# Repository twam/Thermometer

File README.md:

# Thermometer

## Sensor-Board

Connector: [Omega PCC-SMP-K](https://www.omega.com/en-us/temperature-measurement/temperature-connectors%2C-panels-and-block-assemblies/temperature-connectors/p/PCC-OST-SMP)

Chip: [MAX31856](https://datasheets.maximintegrated.com/en/ds/MAX31856.pdf)

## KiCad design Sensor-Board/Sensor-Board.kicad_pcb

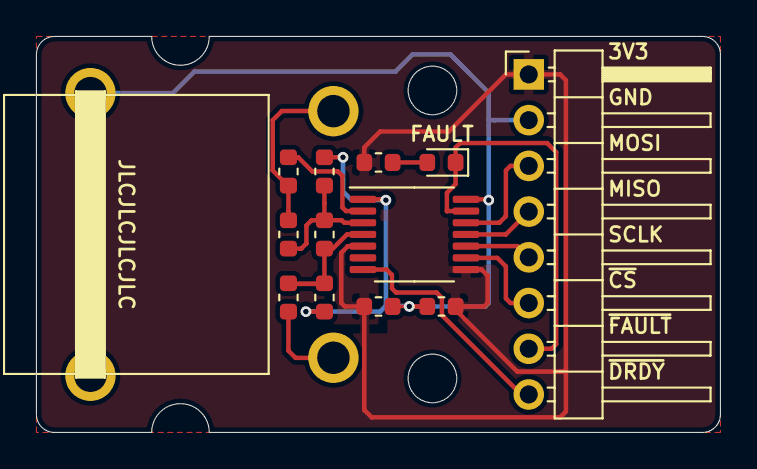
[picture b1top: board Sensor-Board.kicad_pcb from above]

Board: 2 copper layers, 38.0 x 22.0 mm, 13 parts (0 on the bottom side), 14 nets.

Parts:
C11, C12, C13, C14, C15: 100n/50V; C_0603_1608Metric
D11: Red; LED_0603_1608Metric
J1: Sensor; PCC-SMP-K
J2: Conn_01x08; PinHeader_1x08_P2.54mm_Horizontal
R11, R12, R13, R14: R_Small; R_0603_1608Metric
U1: MAX31856; TSSOP-14_4.4x5mm_P0.65mm

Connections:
+3V3: C11.1, C12.1, J2.1, R14.1, U1.5, U1.8
/MISO: J2.4, U1.11
/MOSI: J2.3, U1.12
/SCLK: J2.5, U1.10
/~CS: J2.6, U1.9
/~DRDY: J2.8, U1.7
/~FAULT: D11.1, J2.7, U1.13
GND: C11.2, C12.2, C13.1, C15.2, J1.SH, J2.2, U1.1, U1.14
unnamed: C13.2, C14.1, R11.2, U1.4
unnamed: C14.2, C15.1, R12.2, U1.3
unnamed: D11.2, R14.2
unnamed: J1.1, R12.1, R13.1
unnamed: J1.2, R11.1
unnamed: R13.2, U1.2

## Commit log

2021-01-11 Add README
2021-01-11 Add link to connector/chip

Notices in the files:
Sensor-Board/Sensor-Board.kicad_pcb:
License: Attribution-NonCommercial-ShareAlike 4.0 International (CC BY-NC-SA 4.0)
